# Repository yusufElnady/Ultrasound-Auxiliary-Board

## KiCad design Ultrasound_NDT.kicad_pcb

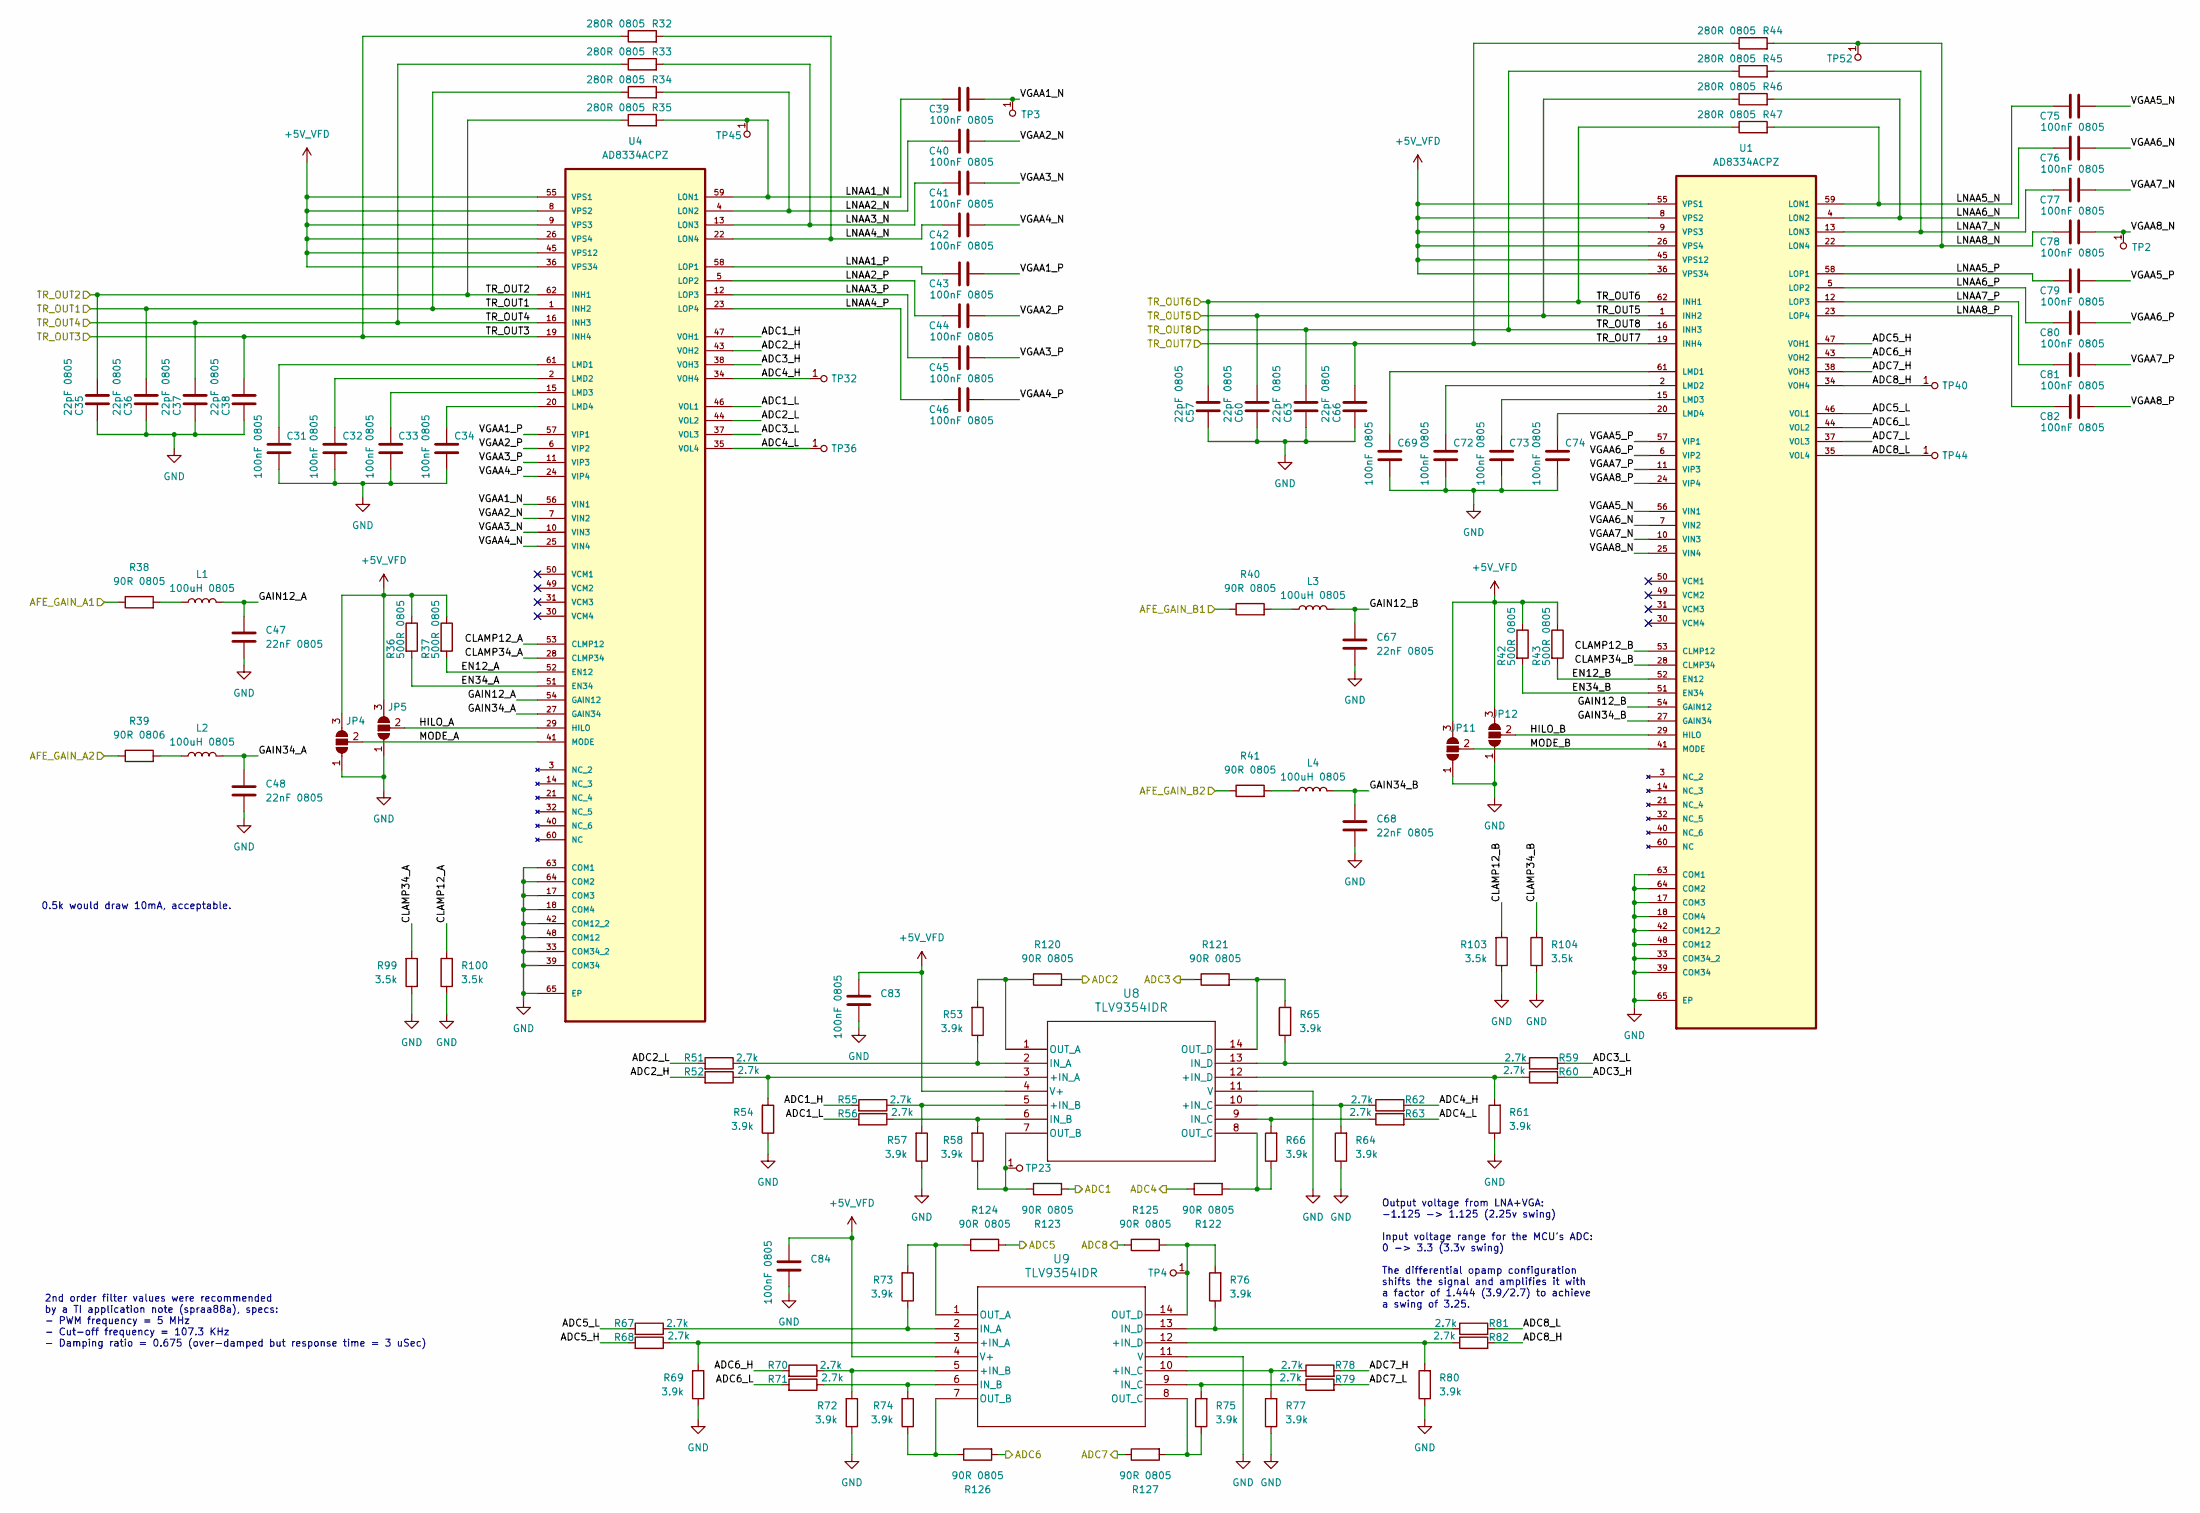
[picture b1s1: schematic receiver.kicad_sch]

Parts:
C31, C32, C33, C34, C39, C40, C41, C42, C43, C44, C45, C46, C69, C72, C73, C74, C75, C76, C77, C78, C79, C80, C81, C82, C83, C84: 100nF 0805; C_0603_1608Metric
C35, C36, C37, C38, C57, C60, C63, C66: 22pF 0805; C_0603_1608Metric
C47, C48, C67, C68: 22nF 0805; C_0603_1608Metric
JP4, JP5, JP11, JP12: SolderJumper_3_Open; SolderJumper-3_P1.3mm_Open_Pad1.0x1.5mm
L1, L2, L3, L4: 100uH 0805; L_0805_2012Metric
R32, R33, R34, R35, R44, R45, R46, R47: 280R 0805; R_0603_1608Metric
R36, R37, R42, R43: 500R 0805; R_0603_1608Metric
R38, R40, R41, R120, R121, R122, R123, R124, R125, R126, R127: 90R 0805; R_0603_1608Metric
R39: 90R 0806; R_0603_1608Metric
R51, R52, R55, R56, R59, R60, R62, R63, R67, R68, R70, R71, R78, R79, R81, R82: 2.7k; R_0603_1608Metric
R53, R54, R57, R58, R61, R64, R65, R66, R69, R72, R73, R74, R75, R76, R77, R80: 3.9k; R_0603_1608Metric
R99, R100, R103, R104: 3.5k; R_0603_1608Metric
TP2, TP3, TP4, TP23, TP32, TP36, TP40, TP44, TP45, TP52: RCT-0C; PROBE_PAD_0805; MPN RCT-0C; Digi-Key_PN A106144CT-ND
U1, U4: AD8334ACPZ; QFN50P900X900X100-65N; MPN AD8334ACPZ
U8, U9: TLV9354IDR; SOIC_9354IDR_TEX

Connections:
+5V_VFD: C83.1, C84.1, JP4.3 (B), JP5.3 (B), JP11.3 (B), JP12.3 (B), R36.1, R37.1, R42.1, R43.1, U1.8 (VPS2), U1.9 (VPS3), U1.26 (VPS4), U1.36 (VPS34), U1.45 (VPS12), U1.55 (VPS1), U4.8 (VPS2), U4.9 (VPS3), U4.26 (VPS4), U4.36 (VPS34), U4.45 (VPS12), U4.55 (VPS1), U8.4 (V+), U9.4 (V+); also elsewhere on the board
/Main MCU Section/ADC1: R123.2; also elsewhere on the board
/Main MCU Section/ADC2: R120.2; also elsewhere on the board
/Main MCU Section/ADC3: R121.1; also elsewhere on the board
/Main MCU Section/ADC4: R122.1; also elsewhere on the board
/Main MCU Section/ADC5: R124.2; also elsewhere on the board
/Main MCU Section/ADC6: R126.2; also elsewhere on the board
/Main MCU Section/ADC7: R127.1; also elsewhere on the board
/Main MCU Section/ADC8: R125.1; also elsewhere on the board
/Main MCU Section/AFE_GAIN_A1: R38.1; also elsewhere on the board
/Main MCU Section/AFE_GAIN_A2: R39.1; also elsewhere on the board
/Main MCU Section/AFE_GAIN_B1: R40.1; also elsewhere on the board
/Main MCU Section/AFE_GAIN_B2: R41.1; also elsewhere on the board
/Receiving Section/ADC1_H: R55.2, U4.47 (VOH1)
/Receiving Section/ADC1_L: R56.2, U4.46 (VOL1)
/Receiving Section/ADC2_H: R52.2, U4.43 (VOH2)
/Receiving Section/ADC2_L: R51.2, U4.44 (VOL2)
/Receiving Section/ADC3_H: R60.2, U4.38 (VOH3)
/Receiving Section/ADC3_L: R59.2, U4.37 (VOL3)
/Receiving Section/ADC4_H: R62.2, TP32.1, U4.34 (VOH4)
/Receiving Section/ADC4_L: R63.2, TP36.1, U4.35 (VOL4)
/Receiving Section/ADC5_H: R68.2, U1.47 (VOH1)
/Receiving Section/ADC5_L: R67.2, U1.46 (VOL1)
/Receiving Section/ADC6_H: R70.2, U1.43 (VOH2)
/Receiving Section/ADC6_L: R71.2, U1.44 (VOL2)
/Receiving Section/ADC7_H: R78.2, U1.38 (VOH3)
/Receiving Section/ADC7_L: R79.2, U1.37 (VOL3)
/Receiving Section/ADC8_H: R82.2, TP40.1, U1.34 (VOH4)
/Receiving Section/ADC8_L: R81.2, TP44.1, U1.35 (VOL4)
/Receiving Section/CLAMP12_A: R100.2, U4.53 (CLMP12)
/Receiving Section/CLAMP12_B: R103.2, U1.53 (CLMP12)
/Receiving Section/CLAMP34_A: R99.2, U4.28 (CLMP34)
/Receiving Section/CLAMP34_B: R104.2, U1.28 (CLMP34)
/Receiving Section/EN12_A: R37.2, U4.52 (EN12)
/Receiving Section/EN12_B: R43.2, U1.52 (EN12)
/Receiving Section/EN34_A: R36.2, U4.51 (EN34)
/Receiving Section/EN34_B: R42.2, U1.51 (EN34)
/Receiving Section/GAIN12_A: C47.1, L1.2, U4.54 (GAIN12)
/Receiving Section/GAIN12_B: C67.1, L3.2, U1.54 (GAIN12)
/Receiving Section/GAIN34_A: C48.1, L2.2, U4.27 (GAIN34)
/Receiving Section/GAIN34_B: C68.1, L4.2, U1.27 (GAIN34)
/Receiving Section/HILO_A: JP5.2 (C), U4.29 (HILO)
/Receiving Section/HILO_B: JP12.2 (C), U1.29 (HILO)
/Receiving Section/LNAA1_N: C39.1, R35.2, TP45.1, U4.59 (LON1)
/Receiving Section/LNAA1_P: C43.1, U4.58 (LOP1)
/Receiving Section/LNAA2_N: C40.1, R34.2, U4.4 (LON2)
/Receiving Section/LNAA2_P: C44.1, U4.5 (LOP2)
/Receiving Section/LNAA3_N: C41.1, R33.2, U4.13 (LON3)
/Receiving Section/LNAA3_P: C45.1, U4.12 (LOP3)
/Receiving Section/LNAA4_N: C42.1, R32.2, U4.22 (LON4)
/Receiving Section/LNAA4_P: C46.1, U4.23 (LOP4)
/Receiving Section/LNAA5_N: C75.1, R47.2, U1.59 (LON1)
/Receiving Section/LNAA5_P: C79.1, U1.58 (LOP1)
/Receiving Section/LNAA6_N: C76.1, R46.2, U1.4 (LON2)
/Receiving Section/LNAA6_P: C80.1, U1.5 (LOP2)
/Receiving Section/LNAA7_N: C77.1, R45.2, U1.13 (LON3)
/Receiving Section/LNAA7_P: C81.1, U1.12 (LOP3)
/Receiving Section/LNAA8_N: C78.1, R44.2, TP52.1, U1.22 (LON4)
/Receiving Section/LNAA8_P: C82.1, U1.23 (LOP4)
/Receiving Section/MODE_A: JP4.2 (C), U4.41 (MODE)
/Receiving Section/MODE_B: JP11.2 (C), U1.41 (MODE)
/Receiving Section/TR_OUT1: C36.1, R34.1, U4.1 (INH2); also elsewhere on the board
/Receiving Section/TR_OUT2: C35.1, R35.1, U4.62 (INH1); also elsewhere on the board
/Receiving Section/TR_OUT3: C38.1, R32.1, U4.19 (INH4); also elsewhere on the board
/Receiving Section/TR_OUT4: C37.1, R33.1, U4.16 (INH3); also elsewhere on the board
/Receiving Section/TR_OUT5: C60.1, R46.1, U1.1 (INH2); also elsewhere on the board
/Receiving Section/TR_OUT6: C57.1, R47.1, U1.62 (INH1); also elsewhere on the board
/Receiving Section/TR_OUT7: C66.1, R44.1, U1.19 (INH4); also elsewhere on the board
/Receiving Section/TR_OUT8: C63.1, R45.1, U1.16 (INH3); also elsewhere on the board
/Receiving Section/VGAA1_N: C39.2, TP3.1, U4.56 (VIN1)
/Receiving Section/VGAA1_P: C43.2, U4.57 (VIP1)
/Receiving Section/VGAA2_N: C40.2, U4.7 (VIN2)
/Receiving Section/VGAA2_P: C44.2, U4.6 (VIP2)
/Receiving Section/VGAA3_N: C41.2, U4.10 (VIN3)
/Receiving Section/VGAA3_P: C45.2, U4.11 (VIP3)
/Receiving Section/VGAA4_N: C42.2, U4.25 (VIN4)
/Receiving Section/VGAA4_P: C46.2, U4.24 (VIP4)
/Receiving Section/VGAA5_N: C75.2, U1.56 (VIN1)
/Receiving Section/VGAA5_P: C79.2, U1.57 (VIP1)
/Receiving Section/VGAA6_N: C76.2, U1.7 (VIN2)
/Receiving Section/VGAA6_P: C80.2, U1.6 (VIP2)
/Receiving Section/VGAA7_N: C77.2, U1.10 (VIN3)
/Receiving Section/VGAA7_P: C81.2, U1.11 (VIP3)
/Receiving Section/VGAA8_N: C78.2, TP2.1, U1.25 (VIN4)
/Receiving Section/VGAA8_P: C82.2, U1.24 (VIP4)
GND: C31.2, C32.2, C33.2, C34.2, C35.2, C36.2, C37.2, C38.2, C47.2, C48.2, C57.2, C60.2, C63.2, C66.2, C67.2, C68.2, C69.2, C72.2, C73.2, C74.2, C83.2, C84.2, JP4.1 (A), JP5.1 (A), JP11.1 (A), JP12.1 (A), R54.1, R57.1, R61.1, R64.1, R69.1, R72.1, R77.1, R80.1, R99.1, R100.1, R103.1, R104.1, U1.17 (COM3), U1.18 (COM4), U1.33 (COM34_2), U1.39 (COM34), U1.42 (COM12_2), U1.48 (COM12), U1.63 (COM1), U1.64 (COM2), U1.65 (EP), U4.17 (COM3), U4.18 (COM4), U4.33 (COM34_2), U4.39 (COM34), U4.42 (COM12_2), U4.48 (COM12), U4.63 (COM1), U4.64 (COM2), U4.65 (EP), U8.11 (V), U9.11 (V); also elsewhere on the board
unnamed: L1.1, R38.2
unnamed: L2.1, R39.2
unnamed: L3.1, R40.2
unnamed: L4.1, R41.2
unnamed: C69.1, U1.61 (LMD1)
unnamed: C72.1, U1.2 (LMD2)
unnamed: C73.1, U1.15 (LMD3)
unnamed: C74.1, U1.20 (LMD4)
unnamed: C31.1, U4.61 (LMD1)
unnamed: C32.1, U4.2 (LMD2)
unnamed: C33.1, U4.15 (LMD3)
unnamed: C34.1, U4.20 (LMD4)
unnamed: R52.1, R54.2, U8.3 (+IN_A)
unnamed: R55.1, R57.2, U8.5 (+IN_B)
unnamed: R62.1, R64.2, U8.10 (+IN_C)
unnamed: R60.1, R61.2, U8.12 (+IN_D)
unnamed: R51.1, R53.1, U8.2 (IN_A)
unnamed: R56.1, R58.2, U8.6 (IN_B)
unnamed: R63.1, R66.2, U8.9 (IN_C)
unnamed: R59.1, R65.1, U8.13 (IN_D)
unnamed: R53.2, R120.1, U8.1 (OUT_A)
unnamed: R58.1, R123.1, TP23.1, U8.7 (OUT_B)
unnamed: R66.1, R122.2, U8.8 (OUT_C)
unnamed: R65.2, R121.2, U8.14 (OUT_D)
unnamed: R68.1, R69.2, U9.3 (+IN_A)
unnamed: R70.1, R72.2, U9.5 (+IN_B)
unnamed: R77.2, R78.1, U9.10 (+IN_C)
unnamed: R80.2, R82.1, U9.12 (+IN_D)
unnamed: R67.1, R73.1, U9.2 (IN_A)
unnamed: R71.1, R74.2, U9.6 (IN_B)
unnamed: R75.2, R79.1, U9.9 (IN_C)
unnamed: R76.1, R81.1, U9.13 (IN_D)
unnamed: R73.2, R124.1, U9.1 (OUT_A)
unnamed: R74.1, R126.1, U9.7 (OUT_B)
unnamed: R75.1, R127.2, U9.8 (OUT_C)
unnamed: R76.2, R125.2, TP4.1, U9.14 (OUT_D)

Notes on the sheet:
Output voltage from LNA+VGA: -1.125 -> 1.125 (2.25v swing) Input voltage range for the MCU's ADC: 0 -> 3.3 (3.3v swing) The differential opamp configuration shifts the signal and amplifies it with a factor of 1.444 (3.9/2.7) to achieve a swing of 3.25.
2nd order filter values were recommended by a TI application note (spraa88a), specs: - PWM frequency = 5 MHz - Cut-off frequency = 107.3 KHz - Damping ratio = 0.675 (over-damped but response time = 3 uSec)
0.5k would draw 10mA, acceptable.

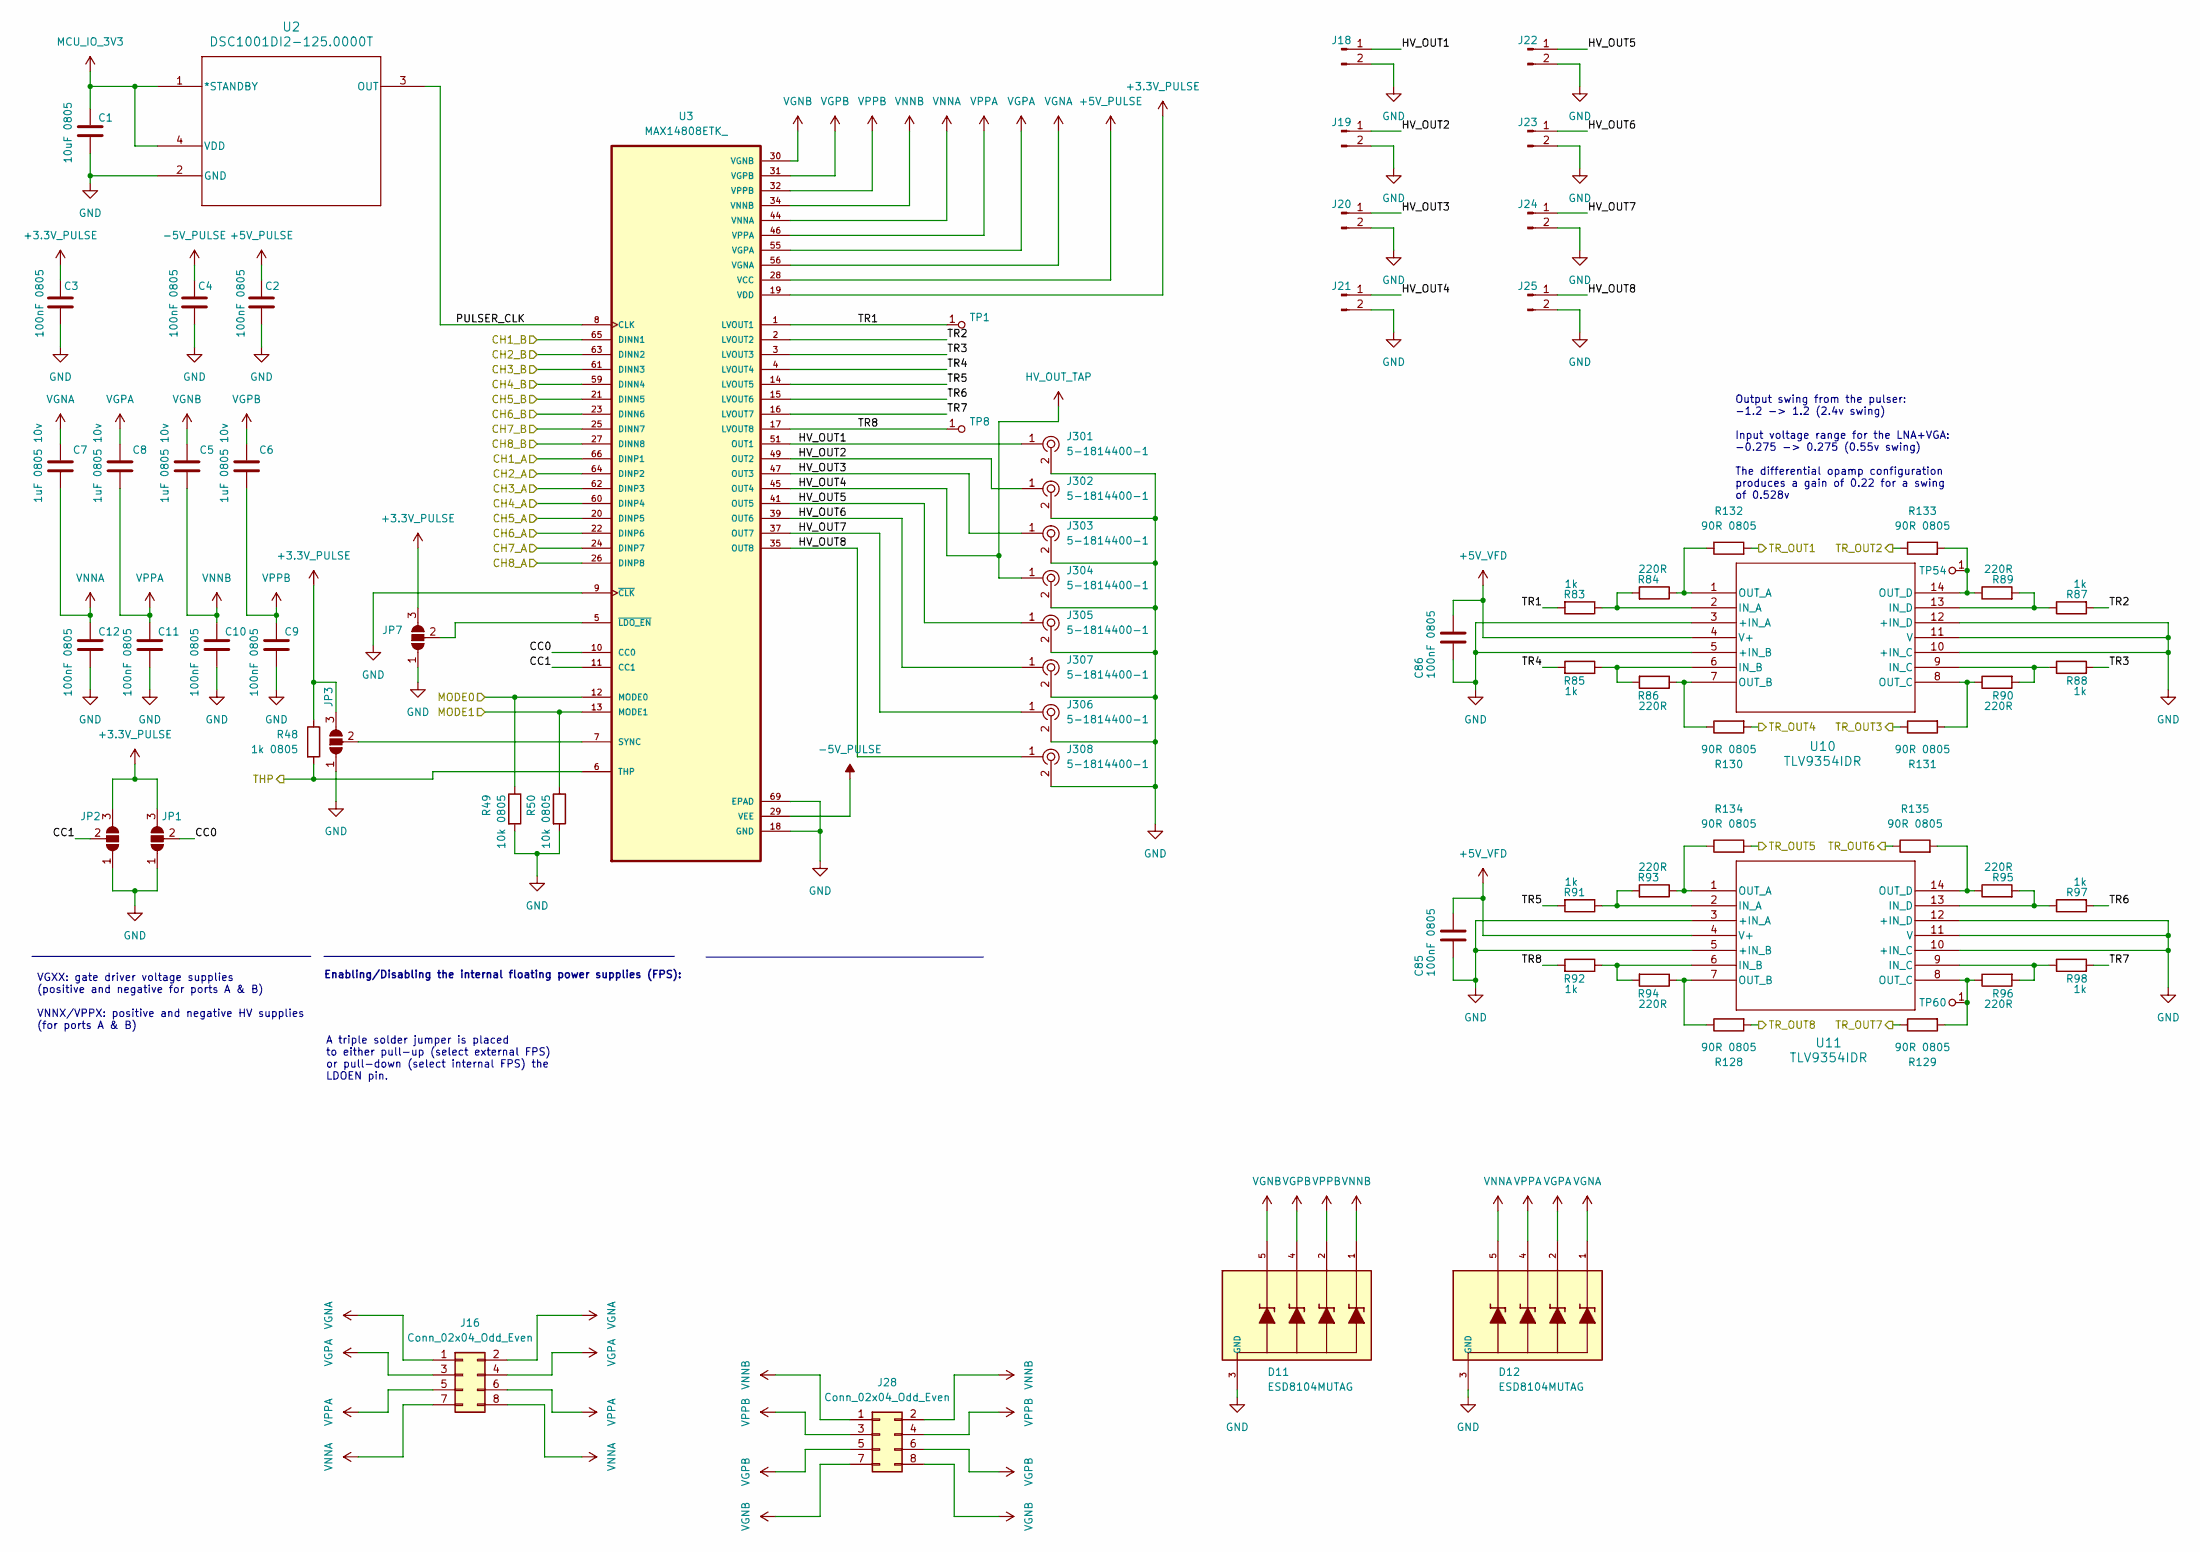
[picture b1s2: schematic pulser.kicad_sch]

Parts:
C1: 10uF 0805; C_0603_1608Metric
C2, C3, C4, C9, C10, C11, C12, C85, C86: 100nF 0805; C_0603_1608Metric
C5, C6, C7, C8: 1uF 0805 10v; C_0603_1608Metric
D11, D12: ESD8104MUTAG; DIO_ESD8104MUTAG; PARTREV 8
J16, J28: Conn_02x04_Odd_Even; PinHeader_2x04_P2.54mm_Vertical
J18, J19, J20, J21, J22, J23, J24, J25: Conn_01x02_Pin; PinHeader_1x02_P2.54mm_Vertical
J301, J302, J303, J304, J305, J306, J307, J308: 5-1814400-1; RF_SMA_RightAngle_5-1814400-1; MPN 5-1814400-1; Digi-Key_PN A97593-ND
JP1, JP2, JP3, JP7: SolderJumper_3_Open; SolderJumper-3_P1.3mm_Open_Pad1.0x1.5mm
R48: 1k 0805; R_0603_1608Metric
R49, R50: 10k 0805; R_0603_1608Metric
R83, R85, R87, R88, R91, R92, R97, R98: 1k; R_0603_1608Metric
R84, R86, R89, R90, R93, R94, R95, R96: 220R; R_0603_1608Metric
R128, R129, R130, R131, R132, R133, R134, R135: 90R 0805; R_0603_1608Metric
TP1, TP8, TP54, TP60: RCT-0C; PROBE_PAD_0805; MPN RCT-0C; Digi-Key_PN A106144CT-ND
U2: DSC1001DI2-125.0000T; CDFN4_2P5X2_MCH
U3: MAX14808ETK_; QFN50P1000X1000X80-69N
U10, U11: TLV9354IDR; SOIC_9354IDR_TEX

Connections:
+3.3V_PULSE: C3.1, JP1.3 (B), JP2.3 (B), JP3.3 (B), JP7.3 (B), R48.1, U3.19 (VDD), U3.67 (VDD); also elsewhere on the board
+5V_PULSE: C2.1, U3.28 (VCC), U3.58 (VCC); also elsewhere on the board
+5V_VFD: C85.1, C86.1, U10.4 (V+), U11.4 (V+); also elsewhere on the board
-5V_PULSE: C4.1, U3.29 (VEE), U3.57 (VEE); also elsewhere on the board
/Main MCU Section/CH1_A: U3.66 (DINP1); also elsewhere on the board
/Main MCU Section/CH1_B: U3.65 (DINN1); also elsewhere on the board
/Main MCU Section/CH2_A: U3.64 (DINP2); also elsewhere on the board
/Main MCU Section/CH2_B: U3.63 (DINN2); also elsewhere on the board
/Main MCU Section/CH3_A: U3.62 (DINP3); also elsewhere on the board
/Main MCU Section/CH3_B: U3.61 (DINN3); also elsewhere on the board
/Main MCU Section/CH4_A: U3.60 (DINP4); also elsewhere on the board
/Main MCU Section/CH4_B: U3.59 (DINN4); also elsewhere on the board
/Main MCU Section/CH5_A: U3.20 (DINP5); also elsewhere on the board
/Main MCU Section/CH5_B: U3.21 (DINN5); also elsewhere on the board
/Main MCU Section/CH6_A: U3.22 (DINP6); also elsewhere on the board
/Main MCU Section/CH6_B: U3.23 (DINN6); also elsewhere on the board
/Main MCU Section/CH7_A: U3.24 (DINP7); also elsewhere on the board
/Main MCU Section/CH7_B: U3.25 (DINN7); also elsewhere on the board
/Main MCU Section/CH8_A: U3.26 (DINP8); also elsewhere on the board
/Main MCU Section/CH8_B: U3.27 (DINN8); also elsewhere on the board
/Main MCU Section/MODE0: R49.1, U3.12 (MODE0); also elsewhere on the board
/Main MCU Section/MODE1: R50.1, U3.13 (MODE1); also elsewhere on the board
/Main MCU Section/THP: R48.2, U3.6 (THP); also elsewhere on the board
/Pulsing Section/CC0: JP1.2 (C), U3.10 (CC0)
/Pulsing Section/CC1: JP2.2 (C), U3.11 (CC1)
/Pulsing Section/HV_OUT1: J18.1, J301.1, U3.51 (OUT1)
/Pulsing Section/HV_OUT2: J19.1, J302.1, U3.49 (OUT2)
/Pulsing Section/HV_OUT3: J20.1, J303.1, U3.47 (OUT3)
/Pulsing Section/HV_OUT5: J22.1, J305.1, U3.41 (OUT5)
/Pulsing Section/HV_OUT6: J23.1, J307.1, U3.39 (OUT6)
/Pulsing Section/HV_OUT7: J24.1, J306.1, U3.37 (OUT7)
/Pulsing Section/HV_OUT8: J25.1, J308.1, U3.35 (OUT8)
/Pulsing Section/PULSER_CLK: U2.3 (OUT), U3.8 (CLK)
/Pulsing Section/TR1: R83.2, TP1.1, U3.1 (LVOUT1)
/Pulsing Section/TR2: R87.2, U3.2 (LVOUT2)
/Pulsing Section/TR3: R88.2, U3.3 (LVOUT3)
/Pulsing Section/TR4: R85.2, U3.4 (LVOUT4)
/Pulsing Section/TR5: R91.2, U3.14 (LVOUT5)
/Pulsing Section/TR6: R97.2, U3.15 (LVOUT6)
/Pulsing Section/TR7: R98.2, U3.16 (LVOUT7)
/Pulsing Section/TR8: R92.2, TP8.1, U3.17 (LVOUT8)
/Receiving Section/TR_OUT1: R132.2; also elsewhere on the board
/Receiving Section/TR_OUT2: R133.1; also elsewhere on the board
/Receiving Section/TR_OUT3: R131.1; also elsewhere on the board
/Receiving Section/TR_OUT4: R130.2; also elsewhere on the board
/Receiving Section/TR_OUT5: R134.2; also elsewhere on the board
/Receiving Section/TR_OUT6: R135.1; also elsewhere on the board
/Receiving Section/TR_OUT7: R129.1; also elsewhere on the board
/Receiving Section/TR_OUT8: R128.2; also elsewhere on the board
GND: C1.2, C2.2, C3.2, C4.2, C9.2, C10.2, C11.2, C12.2, C85.2, C86.2, D11.3 (GND), D11.8 (GND), D12.3 (GND), D12.8 (GND), J18.2, J19.2, J20.2, J21.2, J22.2, J23.2, J24.2, J25.2, J301.2, J302.2, J303.2, J304.2, J305.2, J306.2, J307.2, J308.2, JP1.1 (A), JP2.1 (A), JP3.1 (A), JP7.1 (A), R49.2, R50.2, U2.2 (GND), U3.9 (~CLK), U3.18 (GND), U3.33 (GND), U3.43 (GND), U3.53 (GND), U3.68 (GND), U3.69 (EPAD), U10.3 (+IN_A), U10.5 (+IN_B), U10.10 (+IN_C), U10.11 (V), U10.12 (+IN_D), U11.3 (+IN_A), U11.5 (+IN_B), U11.10 (+IN_C), U11.11 (V), U11.12 (+IN_D); also elsewhere on the board
HV_OUT_TAP: J21.1, J304.1, U3.45 (OUT4)
MCU_IO_3V3: C1.1, U2.1 (*STANDBY), U2.4 (VDD); also elsewhere on the board
unnamed: JP3.2 (C), U3.7 (SYNC)
unnamed: JP7.2 (C), U3.5 (~LDO_EN)
unnamed: R83.1, R84.2, U10.2 (IN_A)
unnamed: R85.1, R86.2, U10.6 (IN_B)
unnamed: R88.1, R90.2, U10.9 (IN_C)
unnamed: R87.1, R89.2, U10.13 (IN_D)
unnamed: R84.1, R132.1, U10.1 (OUT_A)
unnamed: R86.1, R130.1, U10.7 (OUT_B)
unnamed: R90.1, R131.2, U10.8 (OUT_C)
unnamed: R89.1, R133.2, TP54.1, U10.14 (OUT_D)
unnamed: R91.1, R93.2, U11.2 (IN_A)
unnamed: R92.1, R94.2, U11.6 (IN_B)
unnamed: R96.2, R98.1, U11.9 (IN_C)
unnamed: R95.2, R97.1, U11.13 (IN_D)
unnamed: R93.1, R134.1, U11.1 (OUT_A)
unnamed: R94.1, R128.1, U11.7 (OUT_B)
unnamed: R96.1, R129.2, TP60.1, U11.8 (OUT_C)
unnamed: R95.1, R135.2, U11.14 (OUT_D)
VGNA: C7.1, D12.1, J16.1, J16.2, U3.56 (VGNA)
VGNB: C5.1, D11.5, J28.7, J28.8, U3.30 (VGNB)
VGPA: C8.1, D12.2, J16.3, J16.4, U3.55 (VGPA)
VGPB: C6.1, D11.4, J28.5, J28.6, U3.31 (VGPB)
VNNA: C7.2, C12.1, D12.5, J16.7, J16.8, U3.44 (VNNA), U3.48 (VNNA), U3.52 (VNNA)
VNNB: C5.2, C10.1, D11.1, J28.1, J28.2, U3.34 (VNNB), U3.38 (VNNB), U3.42 (VNNB)
VPPA: C8.2, C11.1, D12.4, J16.5, J16.6, U3.46 (VPPA), U3.50 (VPPA), U3.54 (VPPA)
VPPB: C6.2, C9.1, D11.2, J28.3, J28.4, U3.32 (VPPB), U3.36 (VPPB), U3.40 (VPPB); also elsewhere on the board

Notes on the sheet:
Output swing from the pulser: -1.2 -> 1.2 (2.4v swing) Input voltage range for the LNA+VGA: -0.275 -> 0.275 (0.55v swing) The differential opamp configuration produces a gain of 0.22 for a swing of 0.528v
VGXX: gate driver voltage supplies (positive and negative for ports A & B) VNNX/VPPX: positive and negative HV supplies (for ports A & B)
Enabling/Disabling the internal floating power supplies (FPS):
A triple solder jumper is placed to either pull-up (select external FPS) or pull-down (select internal FPS) the LDOEN pin.
